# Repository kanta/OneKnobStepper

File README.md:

# OneKnobStepper
simple stepper motor driver project

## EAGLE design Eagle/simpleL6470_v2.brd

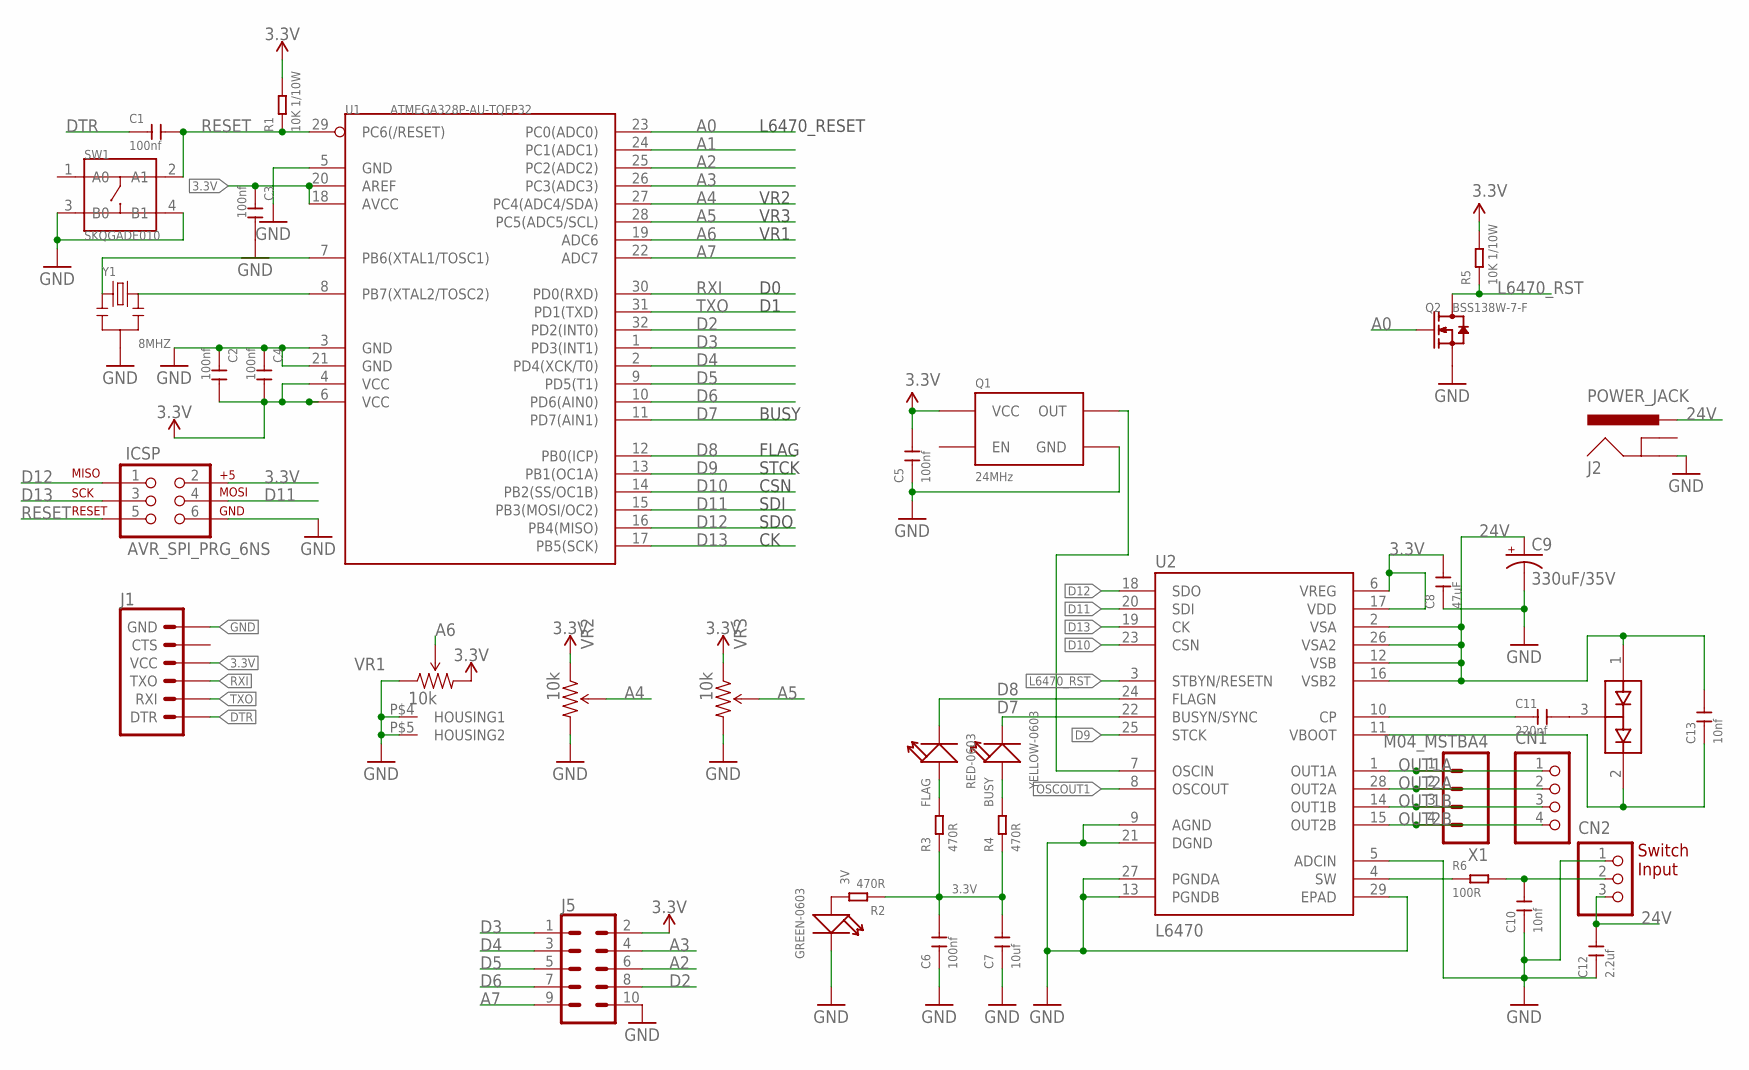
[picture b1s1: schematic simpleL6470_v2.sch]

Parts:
3V: GREEN-0603; LED-0603
BUSY: YELLOW-0603; LED-0603
C1, C2, C3, C4, C5, C6: 100nf; C0603
C7: 10uf; C0805
C8: 47uF; C1206
C9: 330uF/35V; NICHICON_D10
C10: 10nf; C0603
C11: 220nf; C0603
C12: 2.2uf; C0805
C13: 10nf; C0402
CN1: S4B-XASK-1
CN2: B3B-XASK-1
D4: BAV99; SOT23
FLAG: RED-0603; LED-0603
ICSP: AVR_SPI_PRG_6NS; 2X3-NS
J1: 6_PIN_SERIAL_TARGETLOCK; 1X06_LOCK
J2: POWER_JACK; POWER_JACK_PTH
J5: CONN_05X2NO_SILK; 2X5_NOSILK
Q1: 24MHz; CRYSTAL-OSC-SMD-3.2X2.5
Q2: BSS138W-7-F; SOT-23
R1, R5: 10K 1/10W; R0603
R2, R3, R4: 470R; R0603
R6: 100R; R0603
SW1: SKQGADE010; SW4-SMD-5.2X5.2X1.5MM
U1: ATMEGA328P-AU-TQFP32; TQFP32-0.8-7X7MM
U2: L6470; HTSSOP28_NO_THERMAL
VR1: 10k; RK09
VR2, VR3: 10k; TRIMMER_T73XX
X1: M04_MSTBA4; MSTBA4
Y1: 8MHZ; X3-SMD-3.6X1.3X0.8MM

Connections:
3.3V: C2.2, C3.1, C4.2, C5.2, C6.2, C7.2, C8.2, ICSP.2, J1.4 (VCC), J5.2, Q1.4 (VCC), R1.2, R2.1, R3.1, R4.1, R5.2, U1.4 (VCC), U1.6 (VCC), U1.18 (AVCC), U1.20 (AREF), U2.6 (VREG), U2.17 (VDD), VR1.3 (CW), VR2.P$1 (CCW), VR3.P$1 (CCW)
24V: C9.+, C12.2, C13.2, CN2.3, D4.1 (A1), J2.PWR, U2.2 (VSA), U2.12 (VSB), U2.16 (VSB2), U2.26 (VSA2)
A0: Q2.1 (G), U1.23 (PC0(ADC0))
A1: U1.24 (PC1(ADC1))
A2: J5.6, U1.25 (PC2(ADC2))
A3: J5.4, U1.26 (PC3(ADC3))
A4: U1.27 (PC4(ADC4/SDA)), VR2.P$2 (WIPER)
A5: U1.28 (PC5(ADC5/SCL)), VR3.P$2 (WIPER)
A6: U1.19 (ADC6), VR1.2 (WIPER)
A7: J5.9, U1.22 (ADC7)
D2: J5.8, U1.32 (PD2(INT0))
D3: J5.1, U1.1 (PD3(INT1))
D4: J5.3, U1.2 (PD4(XCK/T0))
D5: J5.5, U1.9 (PD5(T1))
D6: J5.7, U1.10 (PD6(AIN0))
D7: BUSY.-, U1.11 (PD7(AIN1)), U2.22 (BUSYN/SYNC)
D8: FLAG.-, U1.12 (PB0(ICP)), U2.24 (FLAGN)
D9: U1.13 (PB1(OC1A)), U2.25 (STCK)
D10: U1.14 (PB2(SS/OC1B)), U2.23 (CSN)
D11: ICSP.4, U1.15 (PB3(MOSI/OC2)), U2.20 (SDI)
D12: ICSP.1, U1.16 (PB4(MISO)), U2.18 (SDO)
D13: ICSP.3, U1.17 (PB5(SCK)), U2.19 (CK)
DTR: C1.1, J1.1 (DTR)
GND: 3V.-, C2.1, C3.2, C4.1, C5.1, C6.1, C7.1, C8.1, C9.-, C10.1, C12.1, CN2.1, ICSP.6, J1.6 (GND), J2.GND, J5.10, Q1.2 (GND), Q2.2 (S), SW1.3 (B0), SW1.4 (B1), U1.3 (GND), U1.5 (GND), U1.21 (GND), U2.5 (ADCIN), U2.9 (AGND), U2.13 (PGNDB), U2.21 (DGND), U2.27 (PGNDA), U2.29 (EPAD), VR1.1 (CCW), VR1.P$4 (HOUSING1), VR1.P$5 (HOUSING2), VR2.P$3 (CW), VR3.P$3 (CW), Y1.2
L6470_RST: Q2.3 (D), R5.1, U2.3 (STBYN/RESETN)
unnamed: FLAG.+, R3.2
unnamed: BUSY.+, R4.2
unnamed: C11.2, D4.3 (COM)
unnamed: 3V.+, R2.2
unnamed: U1.7 (PB6(XTAL1/TOSC1)), Y1.1
unnamed: U1.8 (PB7(XTAL2/TOSC2)), Y1.3
unnamed: C11.1, U2.10 (CP)
unnamed: C13.1, D4.2 (C2), U2.11 (VBOOT)
unnamed: R6.1, U2.4 (SW)
unnamed: C10.2, CN2.2, R6.2
OSCOUT1: U2.8 (OSCOUT)
OUT1A: CN1.1, U2.1 (OUT1A), X1.1
OUT1B: CN1.3, U2.14 (OUT1B), X1.3
OUT2A: CN1.2, U2.28 (OUT2A), X1.2
OUT2B: CN1.4, U2.15 (OUT2B), X1.4
QGOUT: Q1.3 (OUT), U2.7 (OSCIN)
RESET: C1.2, ICSP.5, R1.1, SW1.2 (A1), U1.29 (PC6(/RESET))
RXI: J1.3 (TXO), U1.30 (PD0(RXD))
TXO: J1.2 (RXI), U1.31 (PD1(TXD))

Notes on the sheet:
Switch Input
STCK
CSN
SDI
SDO
BUSY
FLAG
VR1
VR2
VR3
L6470_RESET

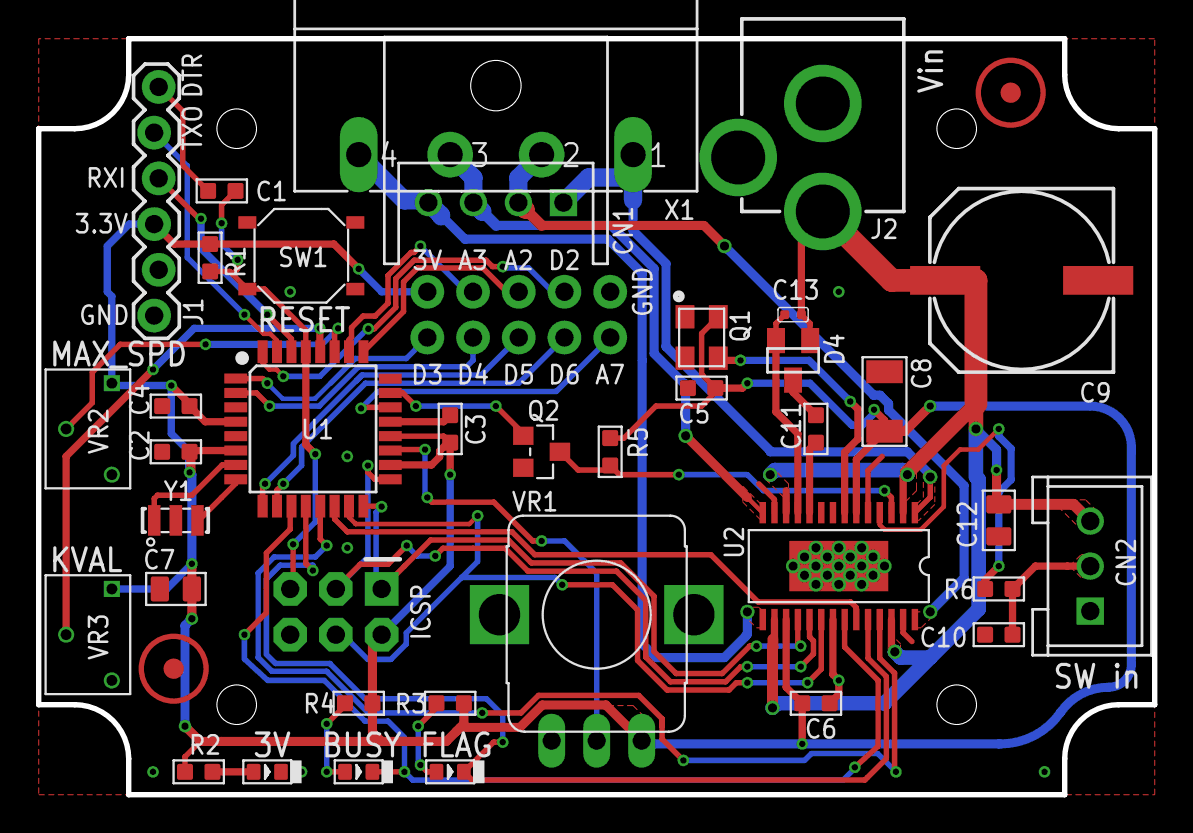
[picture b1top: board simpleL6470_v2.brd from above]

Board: 2 copper layers, 62.0 x 42.0 mm, 42 parts (1 on the bottom side), 42 nets.

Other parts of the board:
U$2, U$3: FIDUCIAL_MARKER_PBAN
U$4: CONFUSEDELECTRONICS_LOGO_12MM

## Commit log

2020-06-12 now based on Sparkfun Autodriver library.
2022-10-13 add VS code files

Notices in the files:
parts and their libraries:
SparkFun-DiscreteSemi: Licensing: Creative Commons ShareAlike 4.0 International - https://creativecommons.org/licenses/by-sa/4.0
SparkFun-PowerIC: Licensing: CC v3.0 Share-Alike You are welcome to use this library for commercial purposes.
